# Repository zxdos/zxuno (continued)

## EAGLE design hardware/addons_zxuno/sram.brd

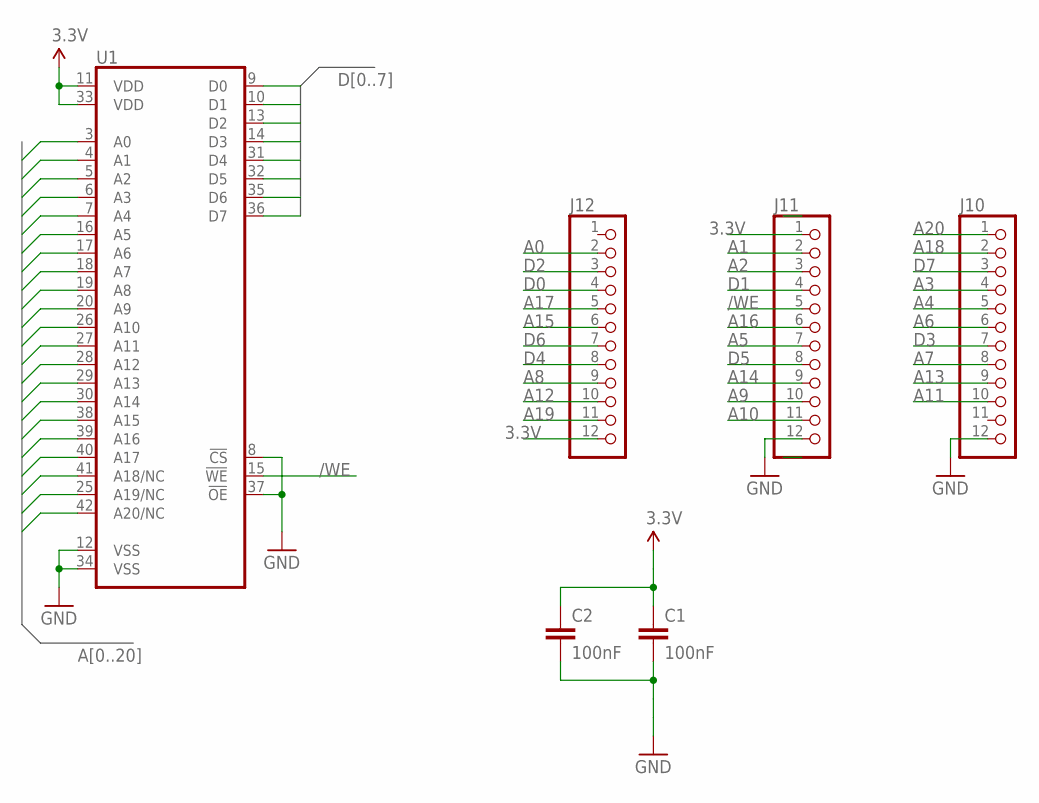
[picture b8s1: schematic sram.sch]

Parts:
C1, C2: 100nF; C0805K
J10, J11, J12: PINHD-1X12; 1X12
U1: ISSI_SRAM_8BIT; TSOP44-II

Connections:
3.3V: C1.1, C2.1, J11.1, J12.12, U1.11 (VDD), U1.33 (VDD)
/WE: J11.5, U1.15 (!WE)
A0: J12.2, U1.3 (A0)
A1: J11.2, U1.4 (A1)
A2: J11.3, U1.5 (A2)
A3: J10.4, U1.6 (A3)
A4: J10.5, U1.7 (A4)
A5: J11.7, U1.16 (A5)
A6: J10.6, U1.17 (A6)
A7: J10.8, U1.18 (A7)
A8: J12.9, U1.19 (A8)
A9: J11.10, U1.20 (A9)
A10: J11.11, U1.26 (A10)
A11: J10.10, U1.27 (A11)
A12: J12.10, U1.28 (A12)
A13: J10.9, U1.29 (A13)
A14: J11.9, U1.30 (A14)
A15: J12.6, U1.38 (A15)
A16: J11.6, U1.39 (A16)
A17: J12.5, U1.40 (A17)
A18: J10.2, U1.41 (A18/NC)
A19: J12.11, U1.25 (A19/NC)
A20: J10.1, U1.42 (A20/NC)
D0: J12.4, U1.9 (D0)
D1: J11.4, U1.10 (D1)
D2: J12.3, U1.13 (D2)
D3: J10.7, U1.14 (D3)
D4: J12.8, U1.31 (D4)
D5: J11.8, U1.32 (D5)
D6: J12.7, U1.35 (D6)
D7: J10.3, U1.36 (D7)
GND: C1.2, C2.2, J10.12, J11.12, U1.8 (!CS), U1.12 (VSS), U1.34 (VSS), U1.37 (!OE)

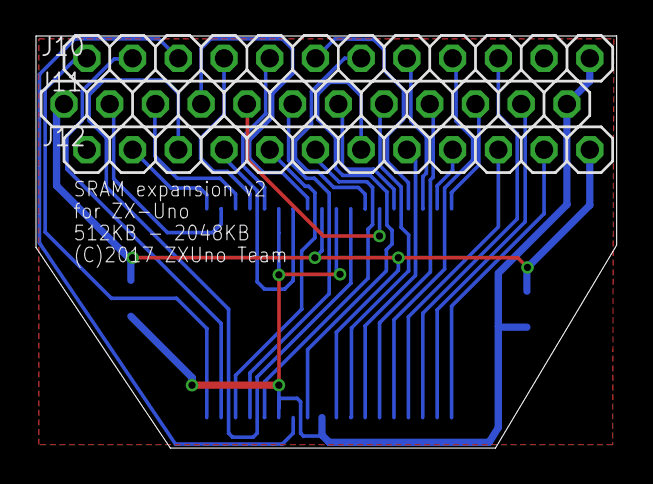
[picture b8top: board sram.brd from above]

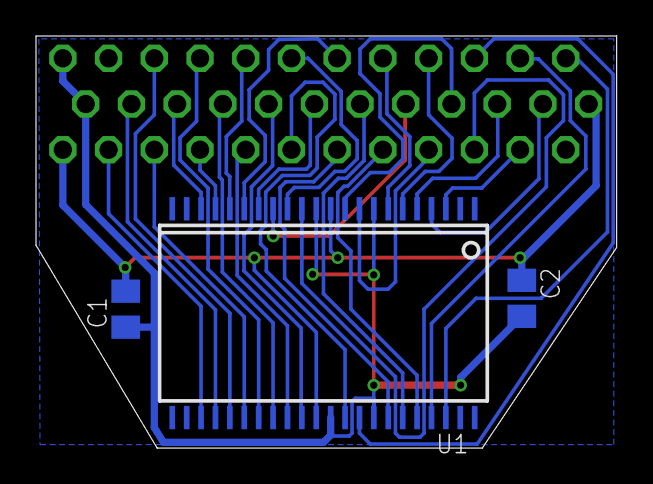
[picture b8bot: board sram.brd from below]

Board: 2 copper layers, 32.3 x 22.9 mm, 6 parts (3 on the bottom side), 32 nets.

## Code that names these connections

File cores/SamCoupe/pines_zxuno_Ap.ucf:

# Clocks & debug
NET "clk50mhz" LOC="P55" | IOSTANDARD = LVCMOS33;
#NET "testled" LOC="2" | IOSTANDARD = LVCMOS33;
NET "clk50mhz" PERIOD=20 ns;
NET "clk12" PERIOD=83 ns;

# Video output
NET "r<2>" LOC="P97" | IOSTANDARD = LVCMOS33;
NET "r<1>" LOC="P95" | IOSTANDARD = LVCMOS33;
NET "r<0>" LOC="P94" | IOSTANDARD = LVCMOS33;
NET "g<2>" LOC="P88" | IOSTANDARD = LVCMOS33;
NET "g<1>" LOC="P87" | IOSTANDARD = LVCMOS33;
NET "g<0>" LOC="P85" | IOSTANDARD = LVCMOS33;
NET "b<2>" LOC="P84" | IOSTANDARD = LVCMOS33;
NET "b<1>" LOC="P83" | IOSTANDARD = LVCMOS33;
NET "b<0>" LOC="P82" | IOSTANDARD = LVCMOS33;
NET "csync" LOC="P93" | IOSTANDARD = LVCMOS33;
#NET "vsync" LOC="P92" | IOSTANDARD = LVCMOS33;
NET "stdn" LOC="P51" | IOSTANDARD = LVCMOS33;
NET "stdnb" LOC="P50" | IOSTANDARD = LVCMOS33;

# Sound input/output
NET "audio_out_left" LOC="P98" | IOSTANDARD = LVCMOS33;
NET "audio_out_right" LOC="P99" | IOSTANDARD = LVCMOS33;
NET "ear" LOC="P1" | IOSTANDARD = LVCMOS33;

# Keyboard and mouse
NET "clkps2" LOC="P143" | IOSTANDARD = LVCMOS33 | PULLUP;     # pin 1 DIN
NET "dataps2" LOC="P142" | IOSTANDARD = LVCMOS33 | PULLUP;    # pin 5 DIN
#NET "mouseclk" LOC="P57" | IOSTANDARD = LVCMOS33 | PULLUP;   # pin 6 DIN
#NET "mousedata" LOC="P56" | IOSTANDARD = LVCMOS33 | PULLUP;  # pin 2 DIN

# SRAM
NET "sram_addr<0>"  LOC="P115" | IOSTANDARD = LVCMOS33;
NET "sram_addr<1>"  LOC="P116" | IOSTANDARD = LVCMOS33;
NET "sram_addr<2>"  LOC="P117" | IOSTANDARD = LVCMOS33;
NET "sram_addr<3>"  LOC="P119" | IOSTANDARD = LVCMOS33;
NET "sram_addr<4>"  LOC="P120" | IOSTANDARD = LVCMOS33;
NET "sram_addr<5>"  LOC="P123" | IOSTANDARD = LVCMOS33;
NET "sram_addr<6>"  LOC="P126" | IOSTANDARD = LVCMOS33;
NET "sram_addr<7>"  LOC="P131" | IOSTANDARD = LVCMOS33;
NET "sram_addr<8>"  LOC="P127" | IOSTANDARD = LVCMOS33;
NET "sram_addr<9>"  LOC="P124" | IOSTANDARD = LVCMOS33;
NET "sram_addr<10>" LOC="P118" | IOSTANDARD = LVCMOS33;
NET "sram_addr<11>" LOC="P121" | IOSTANDARD = LVCMOS33;
NET "sram_addr<12>" LOC="P133" | IOSTANDARD = LVCMOS33;
NET "sram_addr<13>" LOC="P132" | IOSTANDARD = LVCMOS33;
NET "sram_addr<14>" LOC="P137" | IOSTANDARD = LVCMOS33;
NET "sram_addr<15>" LOC="P140" | IOSTANDARD = LVCMOS33;
NET "sram_addr<16>" LOC="P139" | IOSTANDARD = LVCMOS33;
NET "sram_addr<17>" LOC="P141" | IOSTANDARD = LVCMOS33;
NET "sram_addr<18>" LOC="P138" | IOSTANDARD = LVCMOS33;

NET "sram_data<0>"  LOC="P114" | IOSTANDARD = LVCMOS33;
NET "sram_data<1>"  LOC="P112" | IOSTANDARD = LVCMOS33;
NET "sram_data<2>"  LOC="P111" | IOSTANDARD = LVCMOS33;
NET "sram_data<3>"  LOC="P105" | IOSTANDARD = LVCMOS33;
NET "sram_data<4>"  LOC="P104" | IOSTANDARD = LVCMOS33;
NET "sram_data<5>"  LOC="P102" | IOSTANDARD = LVCMOS33;
NET "sram_data<6>"  LOC="P101" | IOSTANDARD = LVCMOS33;
NET "sram_data<7>"  LOC="P100" | IOSTANDARD = LVCMOS33;

NET "sram_we_n"     LOC="P134" | IOSTANDARD = LVCMOS33;

# SPI Flash
#NET "flash_cs_n" LOC="P38" | IOSTANDARD = LVCMOS33;
#NET "flash_clk" LOC="P70" | IOSTANDARD = LVCMOS33;
#NET "flash_mosi" LOC="P64" | IOSTANDARD = LVCMOS33;
#NET "flash_miso" LOC="P65" | IOSTANDARD = LVCMOS33;

# SD/MMC
#NET "sd_cs_n" LOC="P78" | IOSTANDARD = LVCMOS33;
#NET "sd_clk" LOC="P80" | IOSTANDARD = LVCMOS33;
#NET "sd_mosi" LOC="P79" | IOSTANDARD = LVCMOS33;
#NET "sd_miso" LOC="P81" | IOSTANDARD = LVCMOS33;

# JOYSTICK
#NET "joyup"    LOC="P74" | IOSTANDARD = LVCMOS33 | PULLUP;    #JOY6
#NET "joydown"  LOC="P67" | IOSTANDARD = LVCMOS33 | PULLUP;  #JOY4
#NET "joyleft"  LOC="P59" | IOSTANDARD = LVCMOS33 | PULLUP;  #JOY3
#NET "joyright" LOC="P58" | IOSTANDARD = LVCMOS33 | PULLUP; #JOY2
#NET "joyfire"  LOC="P75" | IOSTANDARD = LVCMOS33 | PULLUP;  #JOY7

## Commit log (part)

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2021-01-13 actualizo
2021-01-14 Manual 1.3.0 Añadido Miniduino Añadido zx123_tool Añadida recuperación desde MacOS Actualizado a BIOS 0.83 y utilidades asociadas Múltiples correcciones y mejoras
2021-01-20 Manual 1.3.2 Recuperación con Windows y USB-Blaster
2021-02-03 Manual 1.3.4 Correcciones (issue #12) Añadida más información sobre ROMs de Spectrum personalizadas
2021-02-11 Manual 1.3.5 con correcciones varias
2021-03-09 Manual 1.3.7 Core de ZX81 SE BASIC IV Correcciones
2021-03-11 Corregido MD para estar en norma y añadido otro FAQ
2021-03-20 Manual 1.4.0 de ZXDOS+ RTC+I2S+Pizero addon Correcciones varias
2021-03-28 Manual 0.5 (pre-release) de ZXUNO+ Añadidos cores de Commodore PET, VIC-20 y Jupiter ACE
2021-04-02 Manual 1.4.3 de ZXDOS+ Añadido core de Camputers Lynx Añadidas utilidades para TSX y TZX
2021-04-04 Manual 0.7 de ZXUNO+ Pequeñas correciones y mejoras
2021-04-06 modflash/addrom.bat: optimized process of adding new ROM (automated slot number calculation)
2021-04-06 modflash: improve scripts (separate shared lists of ROMs and cores into roms.txt and cores.txt)
2021-04-07 sdk: created `sdk` directory with `common.mk` and `setvars.bat` files
2021-04-08 sdk: added compilation of `sjasmplus` on GNU/Linux
2021-04-10 sdk: fix mistake in path resolving in file `sdk/setvars.sh`
2021-04-12 sdk: use `sjasmplus` release 20190306.1 for building
2021-04-12 sdk: update `README.md`
2021-04-13 + sdk: added MinGW build target + sdk: added `fcut`, `fpad`, `fpoke` tools * sdk: updated `zx7b` tool * sdk: updated `README.md` - hardware: removed old binaries of `fcut` tool * updated some .bat-sc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
2021-04-14 readme.md: added Open-Source FPGA Foundation links
2021-04-14 sdk: added `GenRom` tool to SDK
2021-04-14 modflash: (fix) use `AddItem` tool from SDK
2021-04-14 software/esprst: make esprst be compliant with version 3.0 of the REUSE Specification
2021-04-14 sdk: make SDK almost compliant with version 3.0 of the REUSE Specification
2021-04-14 sdk: added `bin2hex` tool
2021-04-15 sdk: improve `cmake` usage for cross-compilation for Windows platform
2021-04-15 software: added explicit prerequisites for `esprst` in `Makefile`
2021-04-17 Añado bootloader_core21_35.asm
2021-04-17 software/iwconfig: fixed target's name in `Makefile` (`zcc` feature)
2021-04-18 Creo cores especiales
2021-04-18 Subo mapas de flash
2021-04-19 Manual de ZXDOS+ 1.4.7 Añadido core 128 de Kyp Añadido core extra transparente Correcciones varias
2021-04-20 sdk: removed old `sjasmplus.exe`, fixed a typo in `README.md`
2021-04-22 sdk: fix AND operand in `setvars.sh` script
2021-04-24 utils: add copyright and licensing information to some files
2021-04-24 utils: added ability to build `BACKZXD` and `UPGRZXD` * added ability to build `BACKZXD` and `UPGRZXD` in `Makefile` - removed binaries `BACKZXD` and `UPGRZXD`. Use `Makefile` to build from sources
2021-04-24 Makefile: initial commit + added ability to build `utils` and install them into `SD` directory
2021-04-24 utils: used `esxdos` macro when possible
2021-04-24 utils: separated `Print` function into `Print.inc` file
2021-04-24 utils: separated `rdflsh` function into `rdflsh.inc` file
2021-04-24 utils: uploaded `rdflsh.inc`
2021-04-24 utils: separated `rst28` function into `rst28.inc` file
2021-04-24 utils: added internal `VERSION` strings
2021-04-25 utils: added kounch to contributors
2021-04-25 Añado fuentes Bit2Bin.c
2021-04-25 sdk: added `Bit2Bin` tool
2021-04-25 chip-8 for zxuno
    chip-8 for zxuno
2021-04-25 sdk: added missing `rcs.c`
2021-04-25 SD: added `ESPRST` and `IWCONFIG`
2021-04-26 sdk: followed GNU standards in `src/tools/Makefile`
2021-04-26 bug cazado
2021-04-27 sdk: followed GNU standards in `src/sjasmplus.mk`
2021-04-27 firmware/scroll: added missing `lodepng.h` and `lodepng.c` sources
2021-04-28 Manual 0.10 de ZXUNO+ Core de Videopac (preliminar)
2021-05-02 firmware/scroll: added missing sources of `Png2Rcs` tool
2021-05-02 sdk: added/fixed legal stuff
2021-05-03 sdk: added `Png2Rcs` tool
2021-05-03 Manual 0.13 de ZXUNO+ Añadido core de Galaksija
2021-05-04 upgrade esxdos to 0.8.9
2021-05-04 Manual 1.4.9 Actualizadas instrucciones de upgrzxd, etc.
2021-05-05 firmware/scroll: extracted `playstc.bin` and `music.stc` from `music.bin`
2021-05-05 firmware/scroll: added `Makefile`
2021-05-05 firmware/scroll: (fix) forced Win32 build of `FuenteABin` on Windows
2021-05-07 firmware/scroll: added notice in `music.stc.license` file
2021-05-10 Actualizo flash.zx1
2021-05-15 sdk: added `ay.def`, `filestc.def`, `playstc.inc`
2021-05-15 firmware/scroll: updated credits
2021-05-16 Chip-8 core with RGB support
    Added support for RGB and ZXUNO reset keys
2021-05-17 sdk/LICENSES: added `Unlicense` license text
2021-05-17 Updated `utils/Makefile`, `Makefile` to follow GNU standards
2021-05-17 firmware: updated `bootloader.asm` to use new version of `scroll.bin.zx7b`
2021-05-17 Manual 1.5.0 de ZXDOS+
    Se añaden ficheros faltantes
2021-05-23 utils: added `zxunocfg` utility
2021-05-23 chip-8 VGA/RGB/Composite
    Changed pixel size
2021-05-25 sdk/include: added `dzx7b.mac` macros for ZX7 backwards decompressor
2021-05-25 firmware/scroll: added Einar Saukas to contributors
2021-05-25 sdk/windows-x86/bin: added `sjasmplus.exe` to `.gitignore`
2021-06-04 firmware,utils: tiny source code fixes/modifications
2021-06-04 software: added `esxdos` with ESXDOS 0.8.9
2021-06-05 software/esxdos: moved downloaded files to `.downloads` directory
2021-06-06 moved from old repository
2021-06-06 software: moved `dmaplayw` utility from `utils`
2021-06-09 sdk: added SDCC version 4.1.0
2021-06-09 sdk/common.mk: fixed `ZCCCFG` varible assignment
2021-06-09 software/joyconf: added `Makefile` sdk/src/sdcc.inc.mk: fixed `prefix` parameter for proper SDCC installation various small improvements
2021-06-11 sdk, software: moved `.downloads` sub-directories into the single one at the root of the project
2021-06-11 software/keymap: added `Makefile`
2021-06-12 software/keymap: added legal stuff
2021-06-12 sdk/include: added `regs.mac` macros to operate on CPU registers
2021-06-13 sdk/include/regs.mac: small improvements
2021-06-13 software/playzxm: added `Makefile`
2021-07-16 Manual 1.1.0 de ZXUNO+ Se añaden instrucciones para FUZIX Se añaden los cores: ZX Spectrum EXP27 (Kyp), ZX Spectrum (Kyp/azesmbog), Apple I, Colour Genie, Flappy Bird, HT-1080Z, Sharp MZ-700, Pong
2021-09-01 Invierto puertos
2021-09-07 Manual 1.2.0 de ZXUNO+ Manual 1.6.0 de ZXDOS+ Manual 1.0.0 de Miniduino Se revisa estilo, se añaden más imágenes y cores
2021-09-11 sdk/src/lodepng/lodepng.c: updated LodePNG to version 20210627
2021-09-11 firmware/scroll/Makefile: added `test` target
2021-09-12 sdk: updated SJAsmPlus by Aprisobal to version 1.18.3
2021-09-12 software/dmaplayw/dmaplayw.asm: optimized using `regs.mac` macros
2021-09-13 firmware/keymaps/: added legal stuff
2021-09-13 moved `firmware/bezel.png` into `firmware/images/bezel.png`
2021-09-16 sdk/README.md: updated `sdk` structure description sdk/common.mk: fixed `ZXSDK` path assignment, added host platform detection sdk/extract.sh: added message for user to wait for the extraction to com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
2021-09-16 firmware/fonts/: initial commit of fonts
2021-09-16 sdk/src/tools/fontconv.c: removed superfluous filename assignments
2021-09-20 sdk: added `USE_Z88DK_VERSION` variable, moved `z88dk` from `$(ZXSDK)/src/z88dk` into `$(ZXSDK_PLATFORM)/opt/z88dk`
2021-09-20 sdk/include/regs.mac: fixed license identifier
2021-09-20 sdk/include/rcs.mac: initial commit
2021-09-23 sdk/extract.sh: (fix) made parameter `--sha256` optional
2021-09-24 sdk/include/rever.mac: initial commit
2021-09-24 firmware/scroll/Makefile: moved all generated files into `build` directory firmware/scroll/.gitignore: initial commit
2021-09-24 firmware/scroll/scroll.asm: code optimizations using `prn6x8f.mac` macros, added comments
2021-09-25 firmware/Makefile: fixed SJAsmPlus branch selection, added file notice firmware/scroll/Makefile: added file notice firmware/scroll/build.bat: added file notice
2021-10-02 Manual 1.6.1 de ZXDOS+ y gomaDOS+ Se actualiza core de ZX81 Correciones varias Manual en formato ePub
2021-10-03 Reorganización de fuentes de manuales
2021-11-01 zx81 port from Mister
2021-12-27 firmware/scroll/.gitignore: added `conf.mk` and `conf.bat` files firmware/scroll: moved `fuente6x8.png` into `fonts` directory firmware/scroll: moved `fondo.atr` and `fondo.png` into `images` directo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
2021-12-27 firmware/images: initial commit of `logo256x192ut.png` and `logo256x192ut.atr` files based on https://github.com/zxdos/zxuno/blob/95a6557b41bf2a0efb059385f4f8f10c7940bf8e/firmware/logo256x192ut.rcs.z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
2022-02-04 Firmware 0.86. -Cambio bit de splitter a devctrl2 bit 5 -Añado nuevos layouts de teclado generados por desubikado
2022-02-16 firmware/Makefile: added initial scripts to compile different firmware versions
2022-03-14 Se revisan los ejemplos
2022-03-30 sdk: updated `sjasmplus` tool by Aprisobal to version 1.19.0
2022-04-29 Actualizo fuentes core última versión
2022-04-29 genero core
2022-04-30 Corrijo ruta de ePub
2022-05-29 Añado sjasmplus
2022-06-05 ZX81 release 20220604 bug solve
2022-09-19 add mc
2022-09-19 muevo MC a sitio correcto
2022-09-23 nuevo plugin ZX1
2022-11-01 actualizo binario
2022-12-29 Arreglo bug
2022-12-29 optimizo también date
2023-01-29 Moved raster fonts from `firmware/fonts/` into `fonts/` directory
2023-02-17 sdk: updated `sjasmplus` tool by Aprisobal to version 1.20.2
2023-03-24 cambio mapa a35t
2023-03-25 rtc.sys bug mcleod
2023-03-25 empiezo plugin ZX3
2023-03-25 bug ZX3
2023-03-25 subo binario
2023-03-25 creo binario
2023-04-05 se me olvidó el ZXD
2023-05-08 arreglo fallo en logo
2023-07-26 arreglo split
2023-07-26 fix ZX3
2023-07-28 Al pulsar 9 en arranque salta a último core cargado con el plugin ZX3
2023-07-30 cambio para recovery
2023-08-20 actualizo plugin hasta 5 slots fix
2023-08-21 actualizo plugin hasta 5 slots fix3
2023-08-24 Added Neo-Geo (Spanish Manual)
2023-08-27 Fixed page breaks and formatting errors
2023-08-27 Added macOS Ventura ARM binaries
2023-08-28 Fixed NeoGeo intro, gamepad/joystick > controller
2023-09-05 adding BIT plugin
2023-09-06 Fixes #113
2023-09-06 Restore missing fpad.exe
2023-09-06 Corrected anchors
2023-09-08 Añado flags roms en mapa de flash
2023-09-12 Pending formatting and revision Added: Elan Enterprise zxp3 Middle Board (Cores, Wi-Fi, MIDI, USB)
2023-09-14 small fixes
2023-09-14 removed Uno-specific VGA 50Hz warning
2023-09-15 Spanish PDF and ePub updated
2023-09-17 Updated spanish PDF and ePub
2023-09-17 PC XT Core (english manual) draft
2023-09-19 More info on I2S and Sigma-Delta Spectrum control registers (spanish)
2023-09-23 Small fixes I2S and Sigma-Delta (hopefully right this time)
2023-09-25 Arreglo bug zx3
2023-09-29 New arcade cores Small corections and fixes
2023-09-30 Updated PDF and ePub (Spanish)
2023-10-03 New Amstrad CPC 6128 core Explanation of gear shift in Out Run (Spanish Only)
2023-10-06 Added 1942, CPS15, zx cores Several fixes Added list of arcade games
2023-10-08 Translated version and date labels
2023-10-11 Recovery with USB-Blaster and Mac or Linux
2023-10-13 Firmware recovery using FT232H FT2232H Format fixes English translation updated (pending review)
2023-10-20 Added ZX Tape website
2023-11-14 Added fatsort explanation Small fixes Added ARC and ROM Builder Added Apple IIe (Spanish) Added all working Jotego Cores (Spanish)
2024-01-26 Added ESPJoy Manual Addes ESPJoy to ZXUNO+ Manual
2024-02-04 Adde Aliens Core
2024-04-20 New Mist mode
2024-07-29 Manual v1.1.0 Added Mega65 and SMS cores Added Mist RTC
